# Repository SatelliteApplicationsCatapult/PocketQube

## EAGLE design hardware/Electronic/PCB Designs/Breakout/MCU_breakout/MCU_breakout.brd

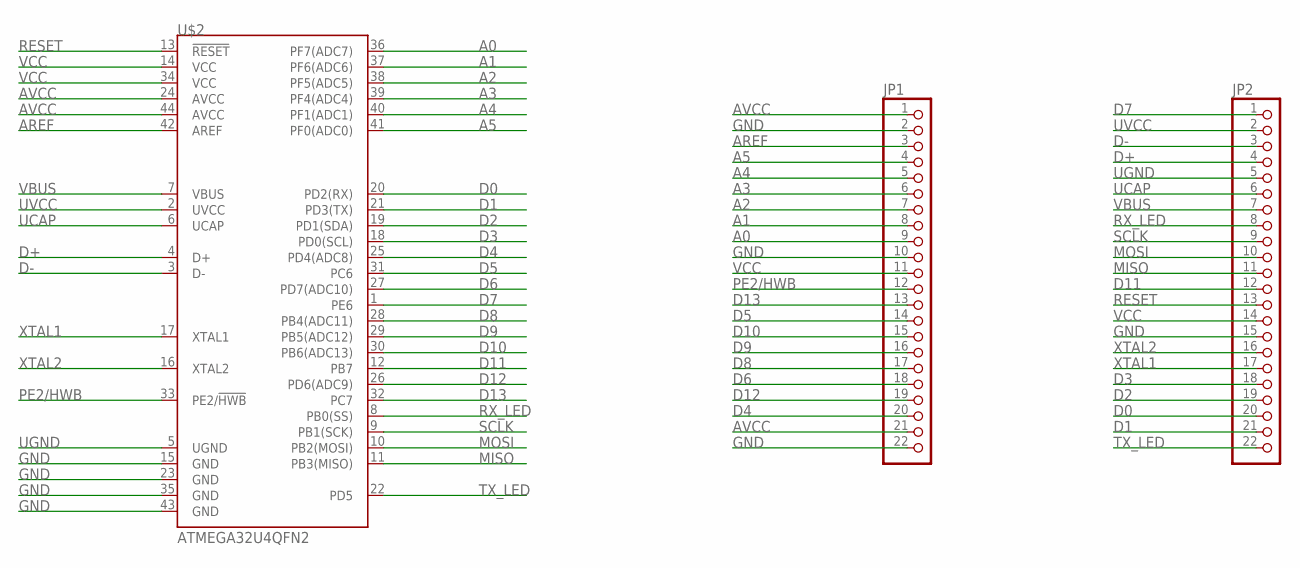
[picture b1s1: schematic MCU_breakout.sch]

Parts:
JP1, JP2: PINHD-1X22; 1X22
U$2: ATMEGA32U4QFN2; QFN-44-NOPAD

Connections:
A0: JP1.9, U$2.36 (PF7(ADC7))
A1: JP1.8, U$2.37 (PF6(ADC6))
A2: JP1.7, U$2.38 (PF5(ADC5))
A3: JP1.6, U$2.39 (PF4(ADC4))
A4: JP1.5, U$2.40 (PF1(ADC1))
A5: JP1.4, U$2.41 (PF0(ADC0))
AREF: JP1.3, U$2.42 (AREF)
AVCC: JP1.1, JP1.21, U$2.24 (AVCC), U$2.44 (AVCC)
D0: JP2.20, U$2.20 (PD2(RX))
D1: JP2.21, U$2.21 (PD3(TX))
D2: JP2.19, U$2.19 (PD1(SDA))
D3: JP2.18, U$2.18 (PD0(SCL))
D4: JP1.20, U$2.25 (PD4(ADC8))
D5: JP1.14, U$2.31 (PC6)
D6: JP1.18, U$2.27 (PD7(ADC10))
D7: JP2.1, U$2.1 (PE6)
D8: JP1.17, U$2.28 (PB4(ADC11))
D9: JP1.16, U$2.29 (PB5(ADC12))
D10: JP1.15, U$2.30 (PB6(ADC13))
D11: JP2.12, U$2.12 (PB7)
D12: JP1.19, U$2.26 (PD6(ADC9))
D13: JP1.13, U$2.32 (PC7)
D+: JP2.4, U$2.4 (D+)
D-: JP2.3, U$2.3 (D-)
GND: JP1.2, JP1.10, JP1.22, JP2.15, U$2.15 (GND), U$2.23 (GND), U$2.35 (GND), U$2.43 (GND)
MISO: JP2.11, U$2.11 (PB3(MISO))
MOSI: JP2.10, U$2.10 (PB2(MOSI))
PE2/HWB: JP1.12, U$2.33 (PE2/!HWB)
RESET: JP2.13, U$2.13 (!RESET)
RX_LED: JP2.8, U$2.8 (PB0(SS))
SCLK: JP2.9, U$2.9 (PB1(SCK))
TX_LED: JP2.22, U$2.22 (PD5)
UCAP: JP2.6, U$2.6 (UCAP)
UGND: JP2.5, U$2.5 (UGND)
UVCC: JP2.2, U$2.2 (UVCC)
VBUS: JP2.7, U$2.7 (VBUS)
VCC: JP1.11, JP2.14, U$2.14 (VCC), U$2.34 (VCC)
XTAL1: JP2.17, U$2.17 (XTAL1)
XTAL2: JP2.16, U$2.16 (XTAL2)

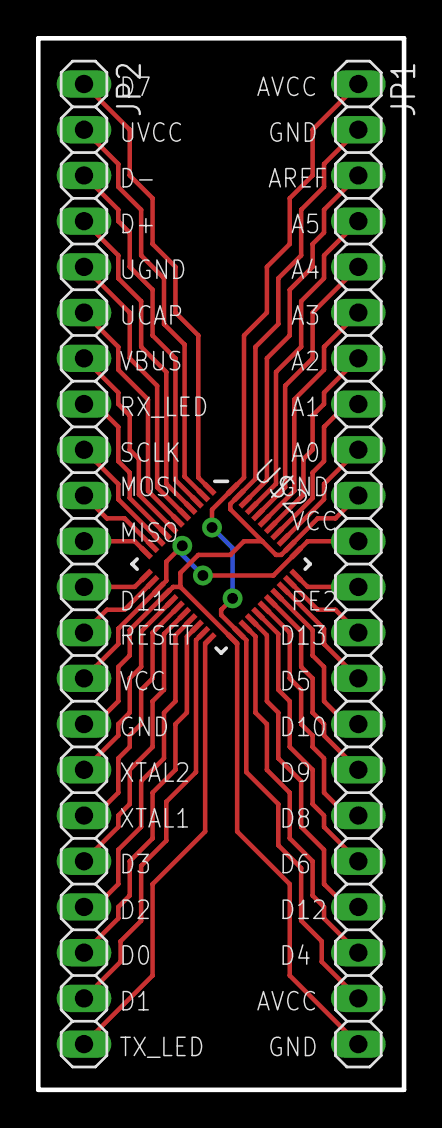
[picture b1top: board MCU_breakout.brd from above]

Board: 2 copper layers, 20.3 x 58.4 mm, 3 parts (0 on the bottom side), 39 nets.

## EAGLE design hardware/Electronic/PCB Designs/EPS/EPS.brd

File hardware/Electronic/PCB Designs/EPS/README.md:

# PQ60 Electrical Power System

### At a glance
The current EPS design features the following basic systems:

1. Four _IXYS_ solar panels as a power source

2. Two _LTC3105_ based MPPT circuits to maximise the solar power generated

3. A _MAX8606ETD_ charge management IC to facilitate safe battery charging and effective system load management.

4. A regulation circuit including:
	* A watchdog timer to detect unresponsive MCUs (_STWD100PYW83F_)
	* A brownout monitor to detect invalid voltages (_BU4231G-TR_)
	* A 3V3 LDO regulator with active-high enable, allowing supervisor ICs or external MCUs to trigger a reset (_MIC5353-3.3YMT_)
	
5. Current monitoring:
	* _FAN4010IL6X_F113_ based high-side unidirectional current sense amplifier ICs to monitor solar output, total 3V3 draw and draw from the battery voltage line on the PQ60 bus
	* _INA211A_ based high-side bi-directional current sense amplifier to monitor total current draw and supply to the battery
	
6. Voltage monitoring:
	* Two MOSFET switched divider networks to measure the MPPT output voltage, the raw battery voltage
	* Direct measurement through MCU ADC of the 3V3 bus voltage
	
7. A 650mAh 3.7V single cell lithium polymer battery

8. Five high-side MOSFET (_NTA4151P & FK3303010L_) switched lines for the __PQ60__ standard, three 3V3 and two raw battery voltage. Each line is reverse polarity protected by the MOSFET and over current protected by a resettable polyfuse (_1206L025YR_)

9. A single _MKL02Z32VFM4_ 32 bit Kinetis MCU, for power management, current and voltage monitoring, line switching and communication with the OBC through I2C

### Usage
Will write something in this section once we actually have an EPS and some code to go with it. Maybe unnecessary if all dealt with through cube library? Will list maximum ratings, tolerances and so on.

### Current design
The current revision of the EPS board uses four __IXYS__ solar panels (_SLMD121H10L-ND_) as a power source, or can also be charged from a standard USB supply. The board contains two Maximum Power Point Tracker (MPPT) circuits based on the __LTC3105__ (_LTC3105EDD#PBF_) DC-DC switching boost regulator, sharing two panels each, with a low forward voltage drop schottkey diode to prevent reverse current leakage from the panels while not illuminated. The output of the MPPT circuits is fed through a twin channel MOSFET based ideal diode IC (_LTC4413_) to the charge management IC (_MAX8606ETD+T_). The total current produced by the MPPT circuits and delivered to the charging IC is monitored by a high side current sense amplifier (_FAN4010IL6X_), and the supply voltage can be measured through a resistor divider network. A MOSFET exists (_NX7002AK_) to disable this divider circuit to prevent current draw when not required. The charge management IC includes integrated load servicing. When the battery voltage exceeds 3.5V, the system output will be internally connected to the battery. Below this voltage, the power supply to the IC will first be used to service the system load, with the remaining available current being used to charge the battery. Both charging sources, the MPPTs and the USB supply, can be disabled if required, in order to obtain accurate battery voltage measurements. The MPPTs can be disabled through a signal to the SHDN input, and the USB supply is connected through a high side switched MOSFET circuit to enable disconnecting. The SHDN signal to the _LTC3105_ MPPTs is connected through an opto-isolator to allow recovery in the event of a fully discharged battery.

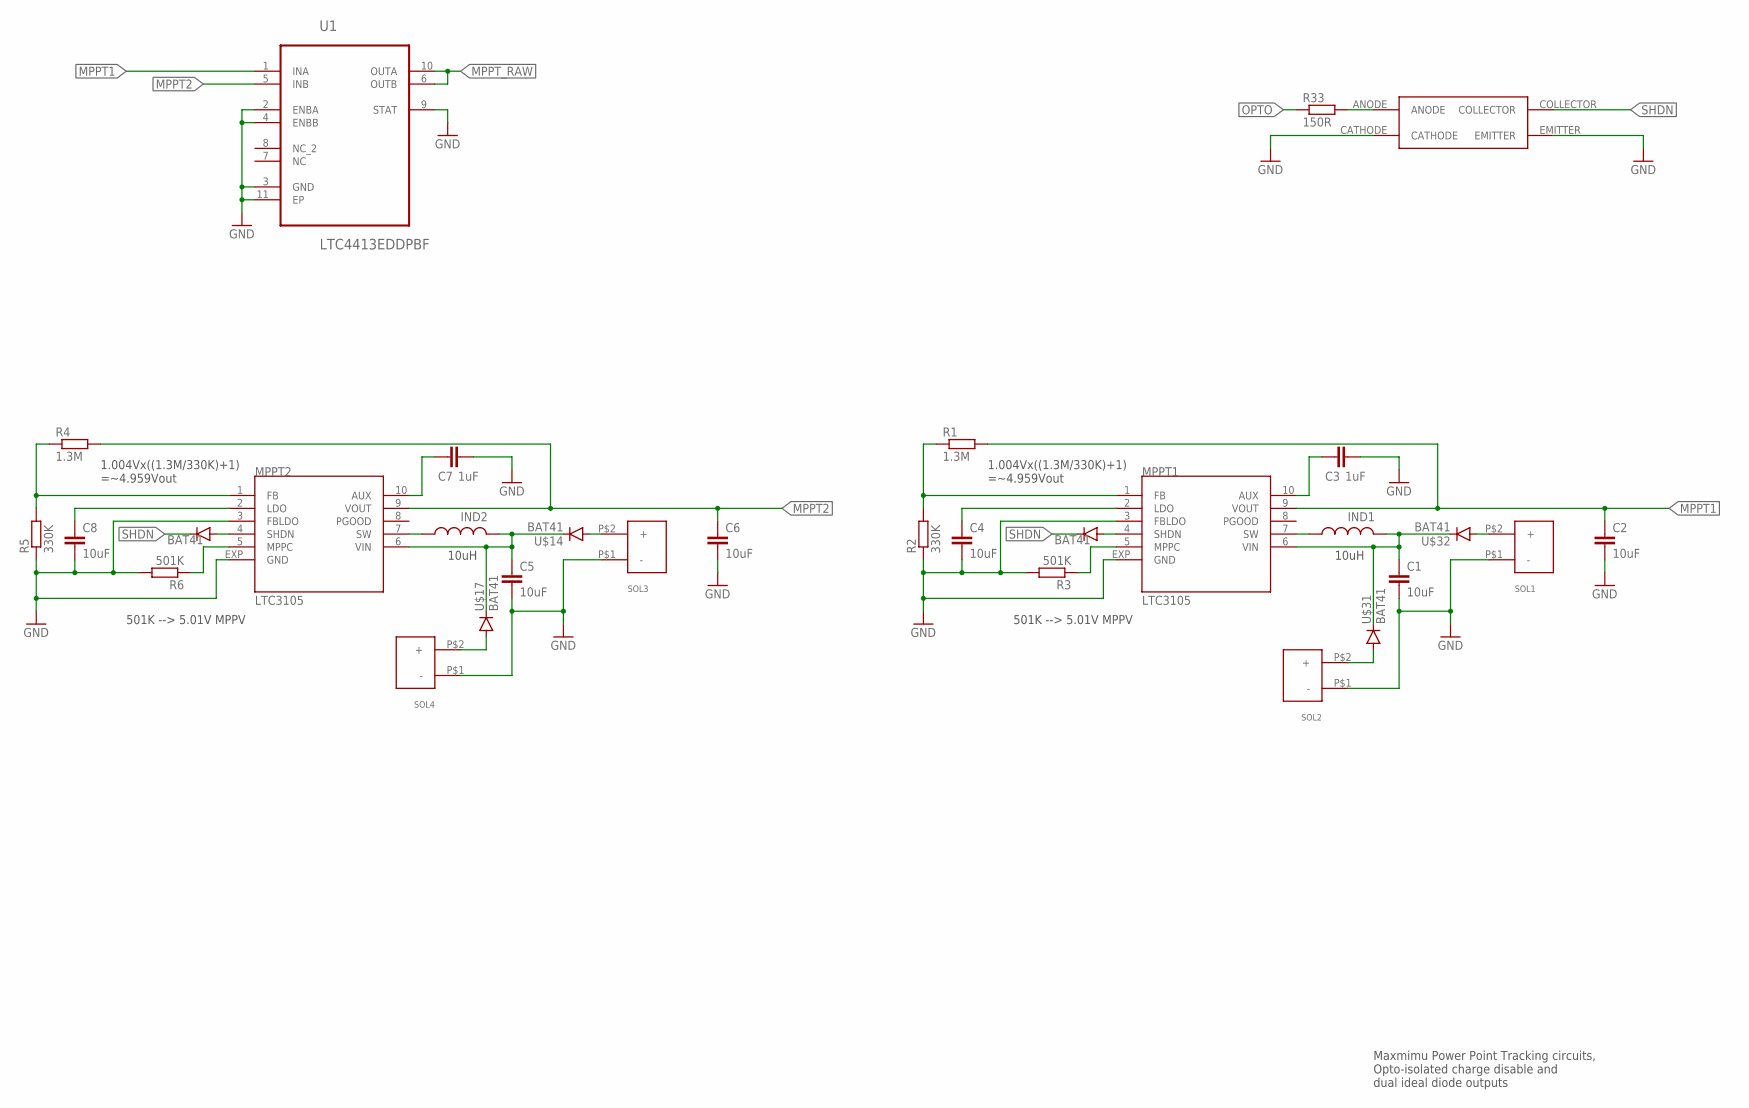
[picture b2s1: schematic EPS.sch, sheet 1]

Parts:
C1, C2, C4, C5, C6, C8: 10uF; C0603
C3, C7: 1uF; C0402
IND1, IND2: WE-TPC-744031100
MPPT1, MPPT2: LTC3105; DFN-3X3
R1, R4: 1.3M; R0402
R2, R5: 330K; R0402
R3, R6: 501K; R0402
R33: 150R; R0402
SOL1, SOL2, SOL3, SOL4: JST-B2B-ZH; JST-B2B-ZR
U1: LTC4413EDDPBF; DFN300X300X80-11N
U$4, U$10, U$14, U$17, U$31, U$32: BAT41; SOD-123
U$24: EL3H7

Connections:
GND: C1.2, C2.2, C3.2, C4.2, C5.2, C6.2, C7.2, C8.2, MPPT1.3 (FBLDO), MPPT1.EXP (GND), MPPT2.3 (FBLDO), MPPT2.EXP (GND), R2.1, R3.2, R5.1, R6.2, SOL1.P$1 (-), SOL2.P$1 (-), SOL3.P$1 (-), SOL4.P$1 (-), U1.2 (ENBA), U1.3 (GND), U1.4 (ENBB), U1.9 (STAT), U1.11 (EP), U$24.CATHODE, U$24.EMITTER; also elsewhere on the board
MPPT1: C2.1, MPPT1.9 (VOUT), R1.2, U1.1 (INA)
MPPT2: C6.1, MPPT2.9 (VOUT), R4.2, U1.5 (INB)
MPPT_RAW: U1.6 (OUTB), U1.10 (OUTA); also elsewhere on the board
unnamed: IND1.P$1 (1), MPPT1.7 (SW)
unnamed: C1.1, IND1.P$3 (2), MPPT1.6 (VIN), U$31.P$1 (C), U$32.P$1 (C)
unnamed: IND2.P$1 (1), MPPT2.7 (SW)
unnamed: C3.1, MPPT1.10 (AUX)
unnamed: C7.1, MPPT2.10 (AUX)
unnamed: C5.1, IND2.P$3 (2), MPPT2.6 (VIN), U$14.P$1 (C), U$17.P$1 (C)
unnamed: MPPT2.1 (FB), R4.1, R5.2
unnamed: C4.1, MPPT1.2 (LDO)
unnamed: MPPT1.1 (FB), R1.1, R2.2
unnamed: MPPT2.5 (MPPC), R6.1
unnamed: C8.1, MPPT2.2 (LDO)
unnamed: MPPT2.4 (SHDN), U$10.P$2 (A)
unnamed: SOL4.P$2 (+), U$17.P$2 (A)
unnamed: MPPT1.4 (SHDN), U$4.P$2 (A)
unnamed: MPPT1.5 (MPPC), R3.1
unnamed: SOL3.P$2 (+), U$14.P$2 (A)
unnamed: SOL2.P$2 (+), U$31.P$2 (A)
unnamed: SOL1.P$2 (+), U$32.P$2 (A)
unnamed: R33.2, U$24.ANODE
OPTO: R33.1; also elsewhere on the board
SHDN: U$4.P$1 (C), U$10.P$1 (C), U$24.COLLECTOR

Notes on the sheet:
10uH
501K --> 5.01V MPPV
1.004Vx((1.3M/330K)+1) =~4.959Vout
Maxmimu Power Point Tracking circuits, Opto-isolated charge disable and dual ideal diode outputs

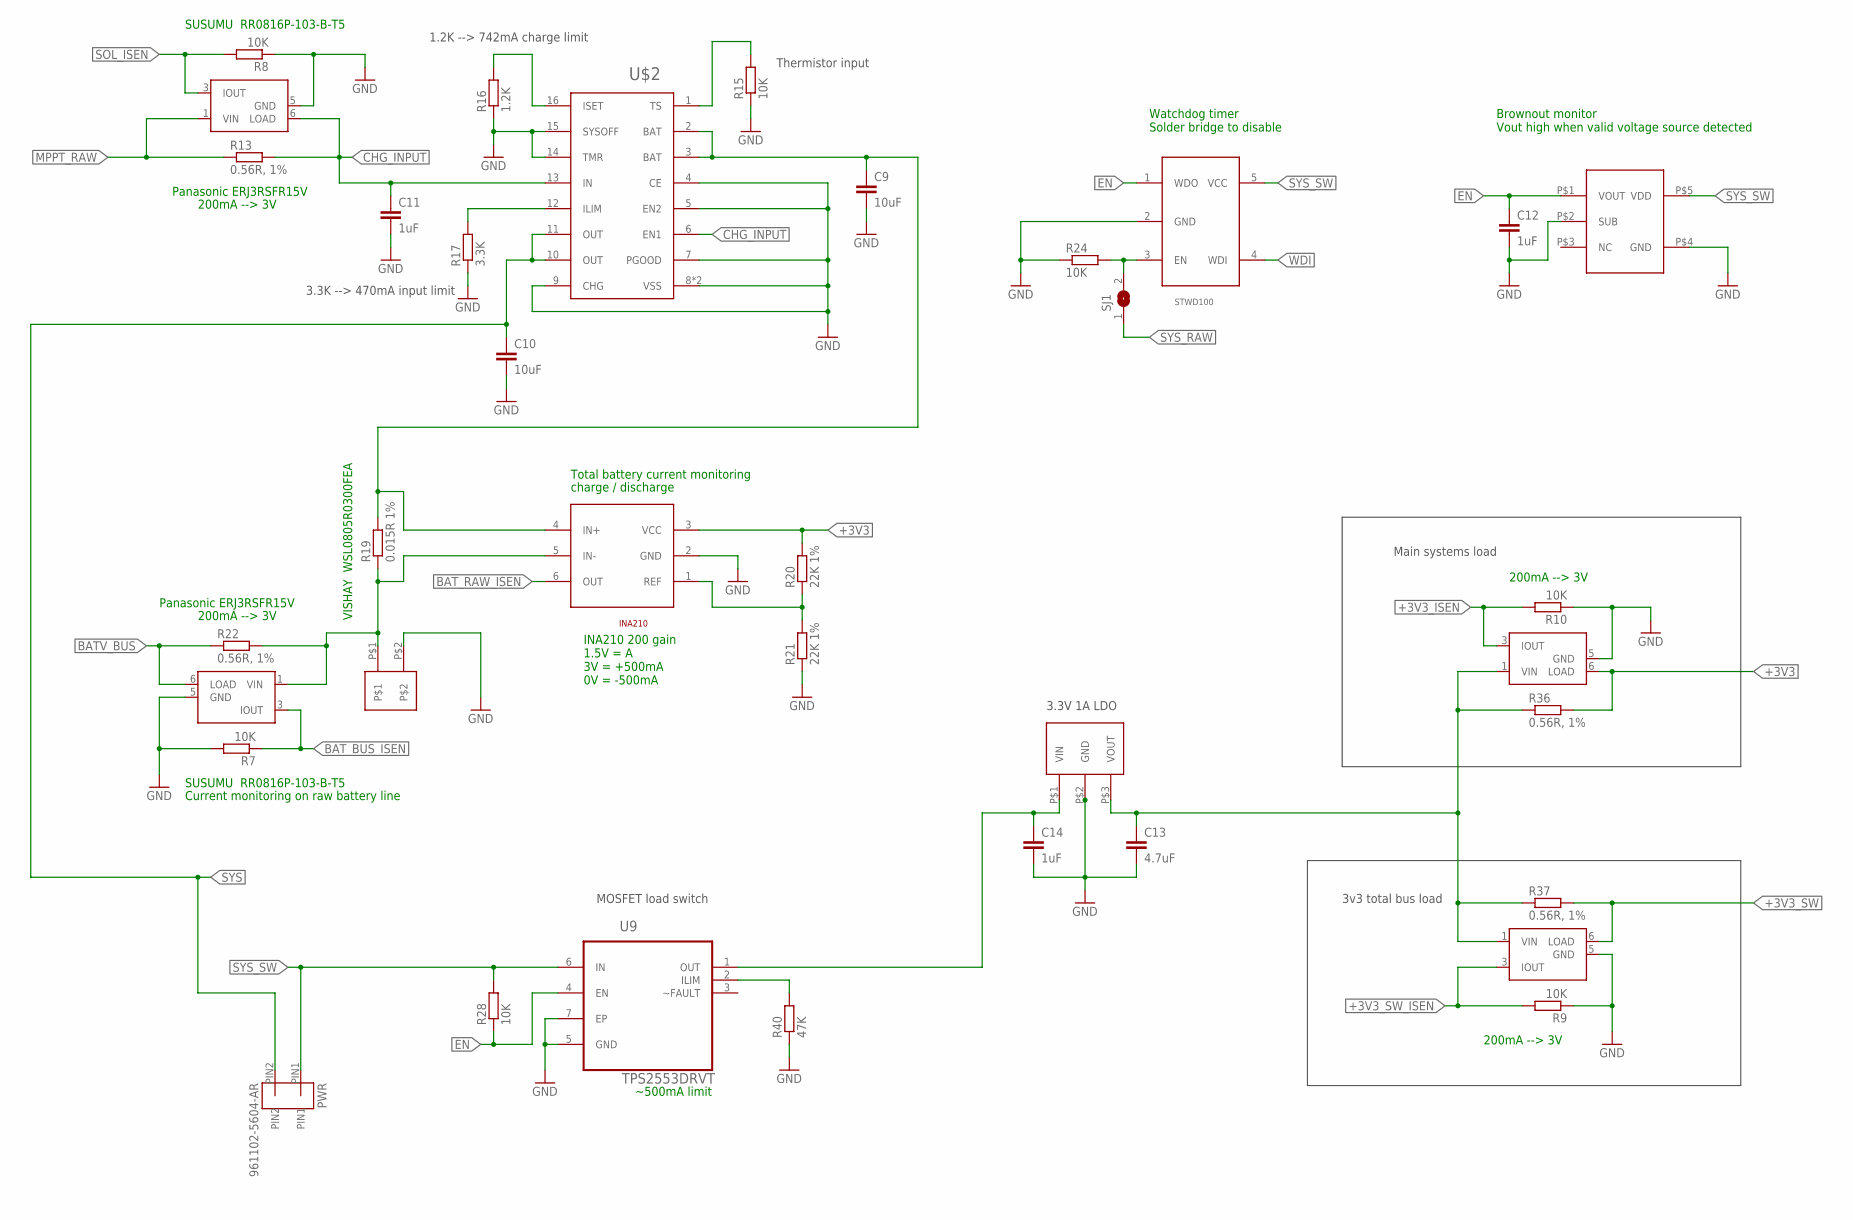
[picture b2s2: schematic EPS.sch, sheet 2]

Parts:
C9, C10: 10uF; C0805
C11, C12, C14: 1uF; C0603
C13: 4.7uF; C0805
INA210: INA211A; SC-70
PWR: 961102-5604-AR
R7, R8, R9, R10, R15, R24, R28: 10K; R0402
R13, R22, R36, R37: 0.56R, 1%; R0603
R16: 1.2K; R0402
R17: 3.3K; R0402
R19: 0.015R 1%; R0603
R20, R21: 22K 1%; R0402
R40: 47K; R0402
SJ1: SJ
STWD100: STWD100PYW83F; SOT_323-5
U9: TPS2553DRVT; SON65P200X200X80-7N
U$2: BQ24079; PVQFN16-THERM
U$3: PICOBLADE53047
U$18, U$19, U$25, U$26: FAN4010IL6X_F113
U$20: MCP1826S; SOT223-3
U$29: BD4835FVE; VSOF5

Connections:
+3V3: INA210.3 (VCC), R20.2, R36.2, U$25.6 (LOAD); also elsewhere on the board
+3V3_ISEN: R10.2, U$25.3 (IOUT); also elsewhere on the board
+3V3_REG: C13.1, R36.1, R37.1, U$20.P$3 (VOUT), U$25.1 (VIN), U$26.1 (VIN)
+3V3_SW: R37.2, U$26.6 (LOAD); also elsewhere on the board
+3V3_SW_ISEN: R9.2, U$26.3 (IOUT); also elsewhere on the board
BATV_BUS: R22.1, U$19.6 (LOAD); also elsewhere on the board
BAT_BUS_ISEN: R7.1, U$19.3 (IOUT); also elsewhere on the board
BAT_RAW_ISEN: INA210.6 (OUT); also elsewhere on the board
CHG_INPUT: C11.1, R13.2, U$2.6 (EN1), U$2.13 (IN), U$18.6 (LOAD); also elsewhere on the board
EN: C12.1, R28.1, STWD100.1 (WDO), U9.4 (EN), U$29.P$1 (VOUT); also elsewhere on the board
GND: C9.2, C10.2, C11.2, C12.2, C13.2, C14.2, INA210.2 (GND), R7.2, R8.1, R9.1, R10.1, R15.1, R16.1, R17.1, R21.1, R24.1, R40.1, STWD100.2 (GND), U9.5 (GND), U9.7 (EP), U$2.4 (CE), U$2.5 (EN2), U$2.7 (PGOOD), U$2.8 (VSS), U$2.9 (CHG), U$2.14 (TMR), U$2.15 (SYSOFF), U$2.17 (VSS), U$3.P$2, U$18.5 (GND), U$19.5 (GND), U$20.P$2 (GND), U$20.P$4 (GND), U$25.5 (GND), U$26.5 (GND), U$29.P$2 (SUB), U$29.P$4 (GND); also elsewhere on the board
MPPT_RAW: R13.1, U$18.1 (VIN); also elsewhere on the board
unnamed: C14.1, U9.1 (OUT), U$20.P$1 (VIN)
unnamed: C9.1, INA210.4 (IN+), R19.2, U$2.2 (BAT), U$2.3 (BAT)
unnamed: R15.2, U$2.1 (TS)
unnamed: R16.2, U$2.16 (ISET)
unnamed: R17.2, U$2.12 (ILIM)
unnamed: INA210.5 (IN-), R19.1, R22.2, U$3.P$1, U$19.1 (VIN)
unnamed: INA210.1 (REF), R20.1, R21.2
unnamed: R24.2, SJ1.2, STWD100.3 (EN)
unnamed: R40.2, U9.2 (ILIM)
SOL_ISEN: R8.2, U$18.3 (IOUT); also elsewhere on the board
SYS: C10.1, PWR.PIN2, U$2.10 (OUT), U$2.11 (OUT)
SYS_RAW: SJ1.1
SYS_SW: PWR.PIN1, R28.2, STWD100.5 (VCC), U9.6 (IN), U$29.P$5 (VDD)
WDI: STWD100.4 (WDI); also elsewhere on the board

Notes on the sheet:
Panasonic ERJ3RSFR15V
200mA --> 3V
SUSUMU RR0816P-103-B-T5
VISHAY WSL0805R0300FEA
Total battery current monitoring
charge / discharge
INA210 200 gain 1.5V = A 3V = +500mA 0V = -500mA
Current monitoring on raw battery line
Main systems load
3v3 total bus load
~500mA limit
Watchdog timer Solder bridge to disable
Brownout monitor Vout high when valid voltage source detected
MOSFET load switch
3.3V 1A LDO
1.2K --> 742mA charge limit
3.3K --> 470mA input limit
Thermistor input

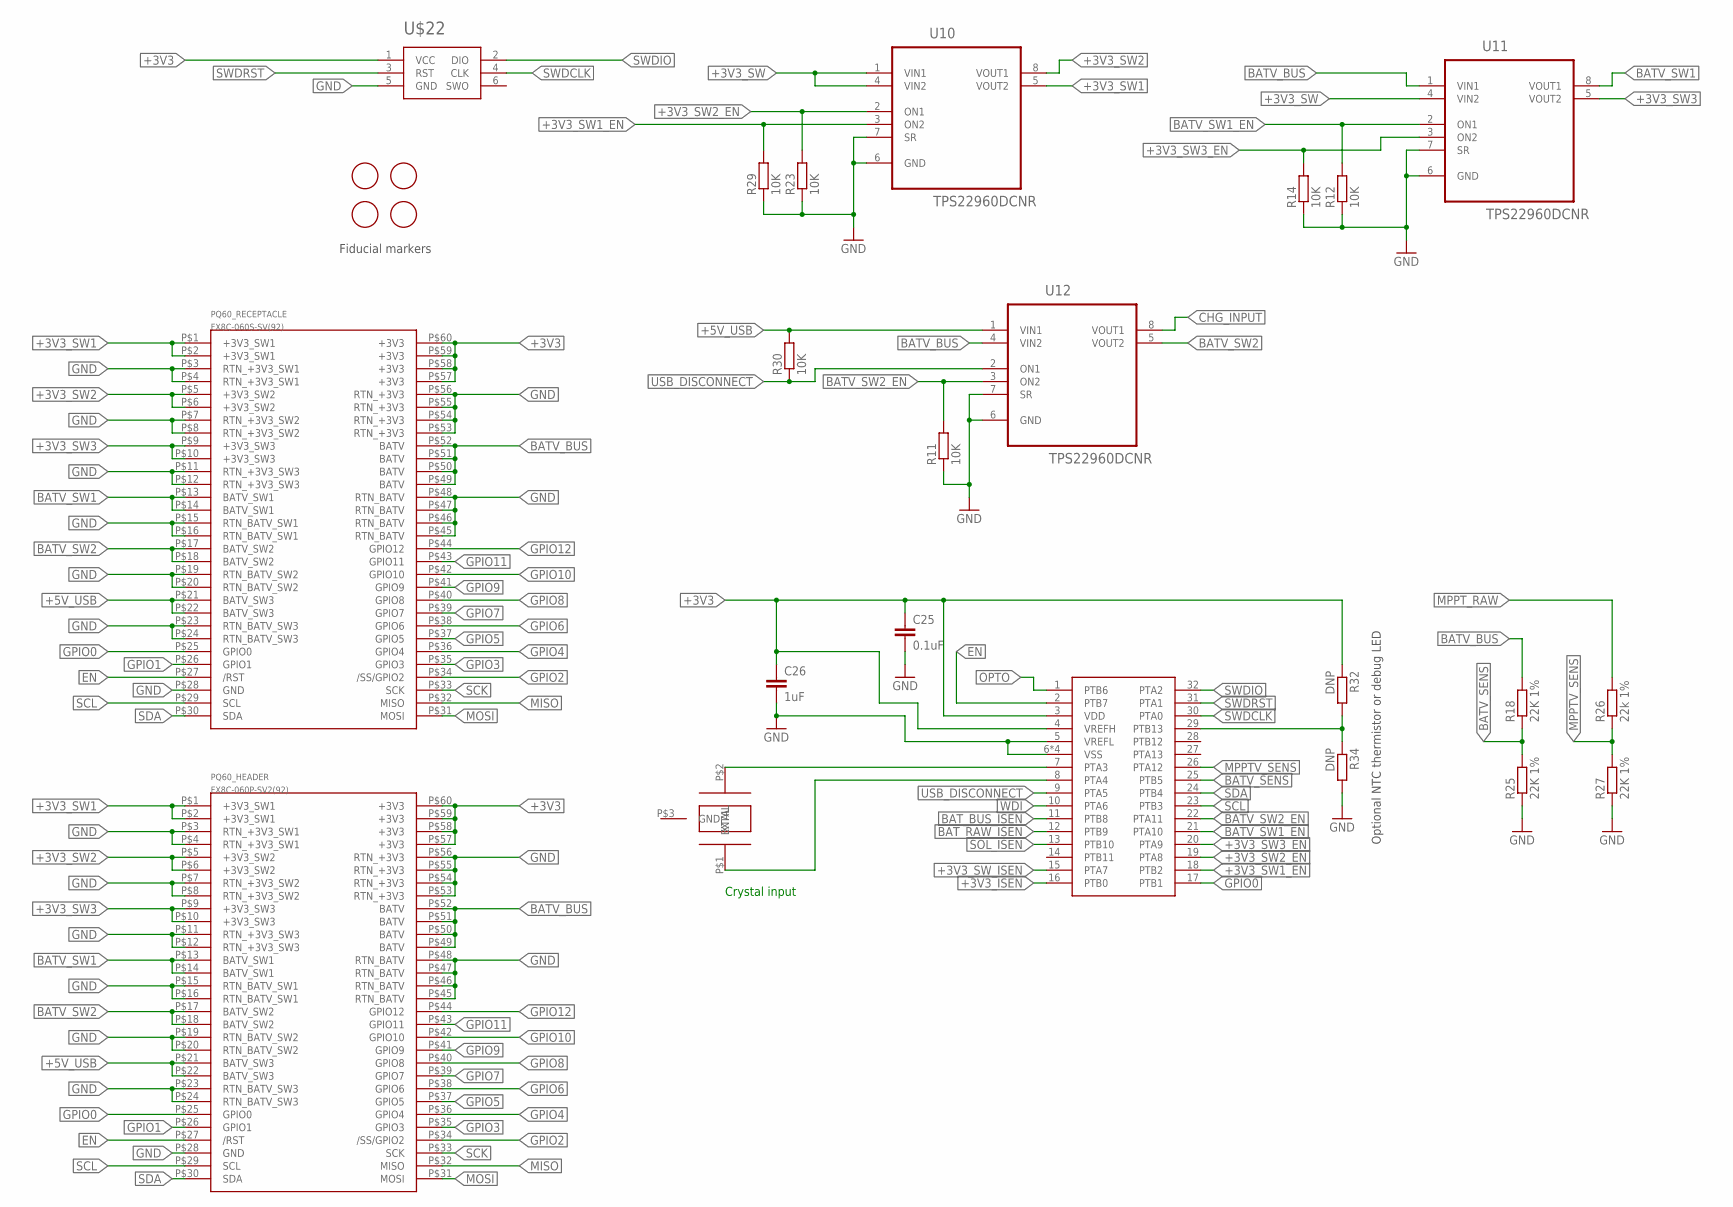
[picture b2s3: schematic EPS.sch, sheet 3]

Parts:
C25: 0.1uF; C0402
C26: 1uF; C0402
FD1, FD2, FD3, FD4: FIDUCIAL; FIDUCIAL_1MM
PQ60_HEADER: FX8C-060P-SV2(92); FX8C-060P-SV(92)
PQ60_RECEPTACLE: FX8C-060S-SV(92)
R11, R12, R14, R23, R29, R30: 10K; R0402
R18, R25, R27: 22K 1%; R0402
R26: 22k 1%; R0402
R32, R34: DNP; R0402
U10, U11, U12: TPS22960DCNR; SOT65P280X145-8N
U$1: AB26TRQ
U$21: MKL02Z16VFM4
U$22: TAG_CONNECT_NO_HOLES

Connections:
+3V3: C25.1, C26.1, PQ60_HEADER.P$57 (+3V3), PQ60_HEADER.P$58 (+3V3), PQ60_HEADER.P$59 (+3V3), PQ60_HEADER.P$60 (+3V3), PQ60_RECEPTACLE.P$57 (+3V3), PQ60_RECEPTACLE.P$58 (+3V3), PQ60_RECEPTACLE.P$59 (+3V3), PQ60_RECEPTACLE.P$60 (+3V3), R32.1, U$21.3 (VDD), U$21.4 (VREFH), U$22.1 (VCC); also elsewhere on the board
+3V3_ISEN: U$21.16 (PTB0); also elsewhere on the board
+3V3_SW: U10.1 (VIN1), U10.4 (VIN2), U11.4 (VIN2); also elsewhere on the board
+3V3_SW1: PQ60_HEADER.P$1 (+3V3_SW1), PQ60_HEADER.P$2 (+3V3_SW1), PQ60_RECEPTACLE.P$1 (+3V3_SW1), PQ60_RECEPTACLE.P$2 (+3V3_SW1), U10.5 (VOUT2)
+3V3_SW1_EN: R29.2, U10.3 (ON2), U$21.18 (PTB2)
+3V3_SW2: PQ60_HEADER.P$5 (+3V3_SW2), PQ60_HEADER.P$6 (+3V3_SW2), PQ60_RECEPTACLE.P$5 (+3V3_SW2), PQ60_RECEPTACLE.P$6 (+3V3_SW2), U10.8 (VOUT1)
+3V3_SW2_EN: R23.2, U10.2 (ON1), U$21.19 (PTA8)
+3V3_SW3: PQ60_HEADER.P$9 (+3V3_SW3), PQ60_HEADER.P$10 (+3V3_SW3), PQ60_RECEPTACLE.P$9 (+3V3_SW3), PQ60_RECEPTACLE.P$10 (+3V3_SW3), U11.5 (VOUT2)
+3V3_SW3_EN: R14.2, U11.3 (ON2), U$21.20 (PTA9)
+3V3_SW_ISEN: U$21.15 (PTA7); also elsewhere on the board
+5V_USB: PQ60_HEADER.P$21 (BATV_SW3), PQ60_HEADER.P$22 (BATV_SW3), PQ60_RECEPTACLE.P$21 (BATV_SW3), PQ60_RECEPTACLE.P$22 (BATV_SW3), R30.2, U12.1 (VIN1)
BATV_BUS: PQ60_HEADER.P$49 (BATV), PQ60_HEADER.P$50 (BATV), PQ60_HEADER.P$51 (BATV), PQ60_HEADER.P$52 (BATV), PQ60_RECEPTACLE.P$49 (BATV), PQ60_RECEPTACLE.P$50 (BATV), PQ60_RECEPTACLE.P$51 (BATV), PQ60_RECEPTACLE.P$52 (BATV), R18.2, U11.1 (VIN1), U12.4 (VIN2); also elsewhere on the board
BATV_SENS: R18.1, R25.2, U$21.25 (PTB5)
BATV_SW1: PQ60_HEADER.P$13 (BATV_SW1), PQ60_HEADER.P$14 (BATV_SW1), PQ60_RECEPTACLE.P$13 (BATV_SW1), PQ60_RECEPTACLE.P$14 (BATV_SW1), U11.8 (VOUT1)
BATV_SW1_EN: R12.2, U11.2 (ON1), U$21.21 (PTA10)
BATV_SW2: PQ60_HEADER.P$17 (BATV_SW2), PQ60_HEADER.P$18 (BATV_SW2), PQ60_RECEPTACLE.P$17 (BATV_SW2), PQ60_RECEPTACLE.P$18 (BATV_SW2), U12.5 (VOUT2)
BATV_SW2_EN: R11.2, U12.3 (ON2), U$21.22 (PTA11)
BAT_BUS_ISEN: U$21.11 (PTB8); also elsewhere on the board
BAT_RAW_ISEN: U$21.12 (PTB9); also elsewhere on the board
CHG_INPUT: U12.8 (VOUT1); also elsewhere on the board
EN: PQ60_HEADER.P$27 (/RST), PQ60_RECEPTACLE.P$27 (/RST), U$21.2 (PTB7); also elsewhere on the board
GND: C25.2, C26.2, PQ60_HEADER.P$3 (RTN_+3V3_SW1), PQ60_HEADER.P$4 (RTN_+3V3_SW1), PQ60_HEADER.P$7 (RTN_+3V3_SW2), PQ60_HEADER.P$8 (RTN_+3V3_SW2), PQ60_HEADER.P$11 (RTN_+3V3_SW3), PQ60_HEADER.P$12 (RTN_+3V3_SW3), PQ60_HEADER.P$15 (RTN_BATV_SW1), PQ60_HEADER.P$16 (RTN_BATV_SW1), PQ60_HEADER.P$19 (RTN_BATV_SW2), PQ60_HEADER.P$20 (RTN_BATV_SW2), PQ60_HEADER.P$23 (RTN_BATV_SW3), PQ60_HEADER.P$24 (RTN_BATV_SW3), PQ60_HEADER.P$28 (GND), PQ60_HEADER.P$45 (RTN_BATV), PQ60_HEADER.P$46 (RTN_BATV), PQ60_HEADER.P$47 (RTN_BATV), PQ60_HEADER.P$48 (RTN_BATV), PQ60_HEADER.P$53 (RTN_+3V3), PQ60_HEADER.P$54 (RTN_+3V3), PQ60_HEADER.P$55 (RTN_+3V3), PQ60_HEADER.P$56 (RTN_+3V3), PQ60_RECEPTACLE.P$3 (RTN_+3V3_SW1), PQ60_RECEPTACLE.P$4 (RTN_+3V3_SW1), PQ60_RECEPTACLE.P$7 (RTN_+3V3_SW2), PQ60_RECEPTACLE.P$8 (RTN_+3V3_SW2), PQ60_RECEPTACLE.P$11 (RTN_+3V3_SW3), PQ60_RECEPTACLE.P$12 (RTN_+3V3_SW3), PQ60_RECEPTACLE.P$15 (RTN_BATV_SW1), PQ60_RECEPTACLE.P$16 (RTN_BATV_SW1), PQ60_RECEPTACLE.P$19 (RTN_BATV_SW2), PQ60_RECEPTACLE.P$20 (RTN_BATV_SW2), PQ60_RECEPTACLE.P$23 (RTN_BATV_SW3), PQ60_RECEPTACLE.P$24 (RTN_BATV_SW3), PQ60_RECEPTACLE.P$28 (GND), PQ60_RECEPTACLE.P$45 (RTN_BATV), PQ60_RECEPTACLE.P$46 (RTN_BATV), PQ60_RECEPTACLE.P$47 (RTN_BATV), PQ60_RECEPTACLE.P$48 (RTN_BATV), PQ60_RECEPTACLE.P$53 (RTN_+3V3), PQ60_RECEPTACLE.P$54 (RTN_+3V3), PQ60_RECEPTACLE.P$55 (RTN_+3V3), PQ60_RECEPTACLE.P$56 (RTN_+3V3), R11.1, R12.1, R14.1, R23.1, R25.1, R27.1, R29.1, R34.2, U10.6 (GND), U10.7 (SR), U11.6 (GND), U11.7 (SR), U12.6 (GND), U12.7 (SR), U$21.5 (VREFL), U$21.6 (VSS), U$21.GND@1 (VSS), U$21.GND@2 (VSS), U$21.GND@3 (VSS), U$22.5 (GND); also elsewhere on the board
GPIO0: PQ60_HEADER.P$25 (GPIO0), PQ60_RECEPTACLE.P$25 (GPIO0), U$21.17 (PTB1)
GPIO1: PQ60_HEADER.P$26 (GPIO1), PQ60_RECEPTACLE.P$26 (GPIO1)
GPIO2: PQ60_HEADER.P$34 (/SS/GPIO2), PQ60_RECEPTACLE.P$34 (/SS/GPIO2)
GPIO3: PQ60_HEADER.P$35 (GPIO3), PQ60_RECEPTACLE.P$35 (GPIO3)
GPIO4: PQ60_HEADER.P$36 (GPIO4), PQ60_RECEPTACLE.P$36 (GPIO4)
GPIO5: PQ60_HEADER.P$37 (GPIO5), PQ60_RECEPTACLE.P$37 (GPIO5)
GPIO6: PQ60_HEADER.P$38 (GPIO6), PQ60_RECEPTACLE.P$38 (GPIO6)
GPIO7: PQ60_HEADER.P$39 (GPIO7), PQ60_RECEPTACLE.P$39 (GPIO7)
GPIO8: PQ60_HEADER.P$40 (GPIO8), PQ60_RECEPTACLE.P$40 (GPIO8)
GPIO9: PQ60_HEADER.P$41 (GPIO9), PQ60_RECEPTACLE.P$41 (GPIO9)
GPIO10: PQ60_HEADER.P$42 (GPIO10), PQ60_RECEPTACLE.P$42 (GPIO10)
GPIO11: PQ60_HEADER.P$43 (GPIO11), PQ60_RECEPTACLE.P$43 (GPIO11)
GPIO12: PQ60_HEADER.P$44 (GPIO12), PQ60_RECEPTACLE.P$44 (GPIO12)
MISO: PQ60_HEADER.P$32 (MISO), PQ60_RECEPTACLE.P$32 (MISO)
MOSI: PQ60_HEADER.P$31 (MOSI), PQ60_RECEPTACLE.P$31 (MOSI)
MPPTV_SENS: R26.1, R27.2, U$21.26 (PTA12)
MPPT_RAW: R26.2; also elsewhere on the board
unnamed: U$1.P$2 (EXTAL), U$21.7 (PTA3)
unnamed: R32.2, R34.1, U$21.29 (PTB13)
unnamed: U$1.P$1 (XTAL), U$21.8 (PTA4)
OPTO: U$21.1 (PTB6); also elsewhere on the board
SCK: PQ60_HEADER.P$33 (SCK), PQ60_RECEPTACLE.P$33 (SCK)
SCL: PQ60_HEADER.P$29 (SCL), PQ60_RECEPTACLE.P$29 (SCL), U$21.23 (PTB3)
SDA: PQ60_HEADER.P$30 (SDA), PQ60_RECEPTACLE.P$30 (SDA), U$21.24 (PTB4)
SOL_ISEN: U$21.13 (PTB10); also elsewhere on the board
SWDCLK: U$21.30 (PTA0), U$22.4 (CLK)
SWDIO: U$21.32 (PTA2), U$22.2 (DIO)
SWDRST: U$21.31 (PTA1), U$22.3 (RST)
USB_DISCONNECT: R30.1, U12.2 (ON1), U$21.9 (PTA5)
WDI: U$21.10 (PTA6); also elsewhere on the board

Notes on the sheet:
Fiducial markers
Optional NTC thermistor or debug LED
Crystal input

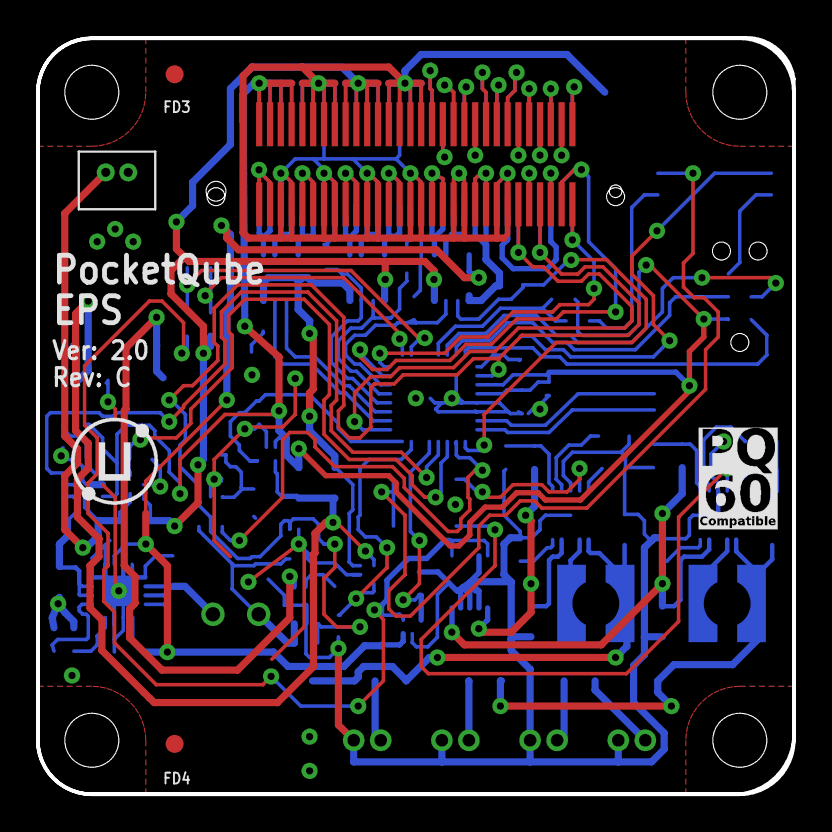
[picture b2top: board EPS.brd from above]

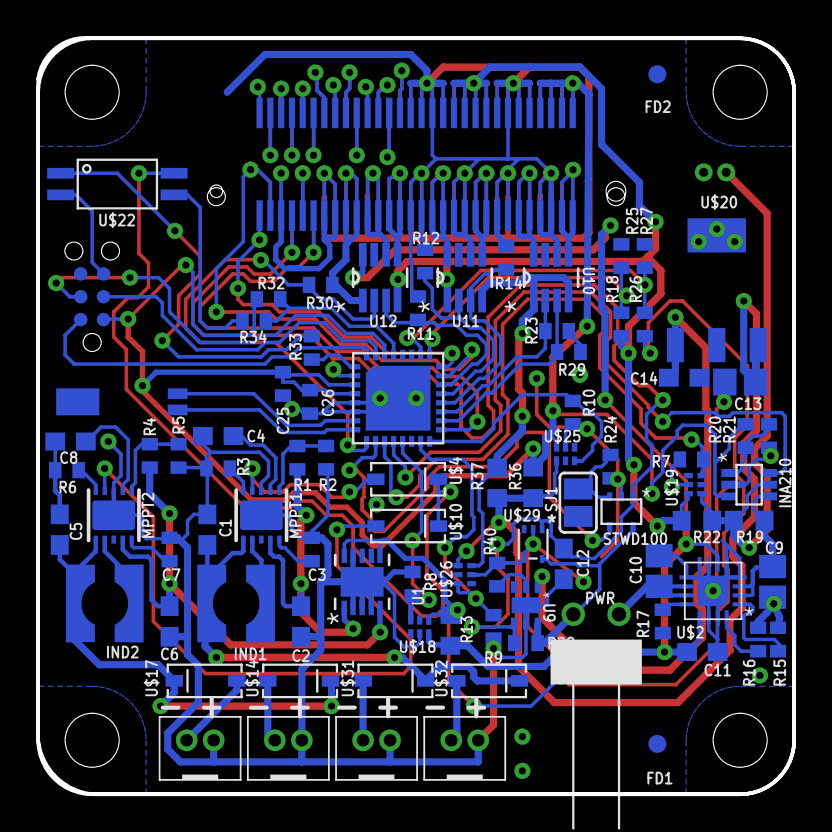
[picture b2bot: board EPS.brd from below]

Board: 2 copper layers, 42.0 x 42.0 mm, 96 parts (89 on the bottom side), 86 nets.

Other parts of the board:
U$9: SA_LOGO_SMALL
U$13: PQ60_CMP
U$35: UBO_LOGO

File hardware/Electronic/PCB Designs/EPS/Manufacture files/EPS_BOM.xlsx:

Parts | Manufacturer | Part number | Value | Qty | Package | Description | Distributor | Order code | Price per | Total | Notes | ROHS | Temp range
C1, C2, C4, C5, C6, C8 |  | C-EUC0603 | 10uF | 6 | C0603 | CAPACITOR, European symbol |  |  |  |  | Any compatible X7R MLCC
C11, C12, C14 |  | C-EUC0603 | 1uF | 3 | C0603 | CAPACITOR, European symbol |  |  |  |  | Any compatible X7R MLCC
C13 |  | C-EUC0805 | 4.7uF | 1 | C0805 | CAPACITOR, European symbol |  |  |  |  | Any compatible X7R MLCC
C25 |  | C-EUC0402 | 0.1uF | 1 | C0402 | CAPACITOR, European symbol |  |  |  |  | Any compatible X7R MLCC
C3, C7, C26 |  | C-EUC0402 | 1uF | 3 | C0402 | CAPACITOR, European symbol |  |  |  |  | Any compatible X7R MLCC
C9, C10 |  | C-EUC0805 | 10uF | 2 | C0805 | CAPACITOR, European symbol |  |  |  |  | Any compatible X7R MLCC
FD1, FD2, FD3, FD4 |  | FIDUCIAL |  | 4 | FIDUCIAL_1MM | For use by pick and place machines to calibrate the vision/machine, 1mm |  |  |  |  | Do not populate
INA210 | Texas Instruments | INA210AIDCKR |  | 1 | SC-70 | Current sense amplifier | Digi-key | 296-38954-1-ND | 1.1000000000000001 | 30.800000000000004 |  | Yes | -40 to 125
IND1, IND2 | Würth | 744031100 |  | 2 | WE-TPC-744031100 | Series Shielded Wire-wound SMD Inductor with a Ferrite Core | Digi-key | 732-1010-1-ND | 1.2230000000000001 | 68.488 | Alternative suppliers available | Yes | -40 to 125
MPPT1, MPPT2 | Linear Technology | LTC3105EMS#PBF |  | 2 | DFN-3X3 | Step-up DC/DC converter | Mouser | 584-LTC3105EMS#PBF | 3.56 | 199.36 |  | Yes | -40 to 85
PQ60_HEADER | Hirose | FX8C-60P-SV6(91) |  | 1 | FX8C-060P-SV(92) | Header | Mouser | 798-FX8C60PSV691 | 2.48 | 69.44 | Alternative suppliers available, however ensure the FX8C60PSV6 part is used, no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 | Yes
PQ60_RECEPTACLE | Hirose | FX8C-60S-SV(91) |  | 1 | FX8C-060S-SV(92) | Socket | Digi-key | H126151-ND | 2.7515999999999998 | 77.044799999999995 | Alternative suppliers available for FX8C60SSV | Yes
PWR | Molex | 90121-0762 |  | 1 | NA | PCB Header, 2.54mm pitch, right angle | Farnell | 9733442 | 0.39100000000000001 | 10.948 |  | Yes | -55 to 125
R1, R4 |  | R-EU_R0402 | 1.3M | 2 | R0402 | RESISTOR, European symbol |  |  |  |  | Any standard chip SMD resistor acceptable, 1% tolerance or better
R13, R22, R36, R37 | Panasonic | ERJ8RQFR56V | 0.56R, 1% | 4 | R0603 | RESISTOR, European symbol | Farnell | 1717849 | 0.14000000000000001 | 15.680000000000001 | Or compatible alternative | Yes | -55 to 125
R16 |  | R-EU_R0402 | 1.2K | 1 | R0402 | RESISTOR, European symbol |  |  |  |  | Any standard chip SMD resistor acceptable, 1% tolerance or better
R17 |  | R-EU_R0402 | 3.3K | 1 | R0402 | RESISTOR, European symbol |  |  |  |  | Any standard chip SMD resistor acceptable, 1% tolerance or better
R18, R20, R21, R25, R27 |  | R-EU_R0402 | 22K 1% | 5 | R0402 | RESISTOR, European symbol |  |  |  |  | Any standard chip SMD resistor acceptable, 1% tolerance or better
R19 | Panasonic | ERJ3BQFR30V | 0.015R 1% | 1 | R0603 | RESISTOR, European symbol | Farnell | 2692819 | 0.18 | 5.04 | Or compatible alternative
R2, R5 |  | R-EU_R0402 | 330K | 2 | R0402 | RESISTOR, European symbol |  |  |  |  | Any standard chip SMD resistor acceptable, 1% tolerance or better
R26 |  | R-EU_R0402 | 22k 1% | 1 | R0402 | RESISTOR, European symbol |  |  |  |  | Any standard chip SMD resistor acceptable, 1% tolerance or better
R3, R6 |  | R-EU_R0402 | 501K | 2 | R0402 | RESISTOR, European symbol |  |  |  |  | Any standard chip SMD resistor acceptable, 1% tolerance or better
R32, R34 |  | R-EU_R0402 |  | 2 | R0402 | RESISTOR, European symbol |  |  |  |  | Do not populate
R33 |  | R-EU_R0402 | 150R | 1 | R0402 | RESISTOR, European symbol |  |  |  |  | Any standard chip SMD resistor acceptable, 1% tolerance or better
R40 |  | R-EU_R0402 | 47K | 1 | R0402 | RESISTOR, European symbol |  |  |  |  | Any standard chip SMD resistor acceptable, 1% tolerance or better
R7, R8, R9, R10, R11, R12, R14, R15, R23, R24, R28, R29, R30 |  | R-EU_R0402 | 10K | 13 | R0402 | RESISTOR, European symbol |  |  |  |  | Any standard chip SMD resistor acceptable, 1% tolerance or better
SJ1 |  | SJ |  | 1 | SJ | SMD solder JUMPER |  |  |  |  | Do not populate
SOL1, SOL2, SOL3, SOL4 | JST | B2B-ZR(LF)(SN) |  | 4 | JST-B2B-ZR | 2-way crimp style Header Connector | Farnell | 9491775 | 6.9699999999999998E-2 | 6.97 | Alternative suppliers available | Yes | -25 to 85
STWD100 | STMicroelectronics | STWD100PYW83F |  | 1 | SOT_323-5 | Watchdog timer circuit | Farnell | 2460853RL | 0.67800000000000005 | 18.984000000000002 | Alternative suppliers available | Yes | -40 to 125
U$1 | Abracon LLC | AB26TRQ |  | 1 | AB26TRQ |  |  |  |  |  | Do not populate
U$18, U$19, U$25, U$26 | ON Semiconductor | FAN4010IL6X-F113 |  | 4 | FAN4010IL6X_F113 | Current sense amplifier | Farnell | 2454632 | 0.34100000000000003 | 38.192 | Alternative suppliers available | Yes | -40 to 85
U$2 | Texas Instruments | BQ24079RGTR |  | 1 | PVQFN16-THERM | Battery Charger for 1 Cell of Li-Ion battery | Farnell | 2492089 | 1.52 | 42.56 | Alternative suppliers available | Yes | -40 to 85
U$20 | Microchip | MCP1826S-3302E/DB |  | 1 | SOT223-3 | Fixed LDO Voltage Regulator | Farnell | 1578424 | 0.47899999999999998 | 13.411999999999999 | Alternative suppliers available | Yes | -40 to 125
U$21 | NXP | MKL02Z16VFM4 |  | 1 | MKL02Z16VFM4 | Microcontroller | Farnell | 2409469 | 1.83 | 51.24 | Alternative suppliers available | Yes | -55 to 150
U$22 |  | TAG_CONNECT_NO_HOLES |  | 1 | TAG_CONNECT_NO_HOLES |  |  |  |  |  | Do not populate
U$24 | Everlight Electronics | EL3H7(TA)-VG |  | 1 | EL3H7 | Phototransistor photocoupler | Digi-key | 1080-1198-1-ND | 0.30399999999999999 | 8.5120000000000005 | Alternative suppliers available | Yes | -55 to 125
U$29 | ROHM Semiconductor | BD4835FVE-TR |  | 1 | VSOF5 | CMOS voltage monitor | Mouser | 755-BD4835FVE-TR | 0.33900000000000002 | 9.4920000000000009 | Or compatible alternative | Yes | -40 to 105
U$3 | Molex | 53047-0210 |  | 1 | PICOBLADE53047 | Wire-to-board header | Farnell | 9733051 | 0.11899999999999999 | 3.3319999999999999 | Alternative suppliers available | Yes | -40 to 85
U$4, U$10, U$14, U$17, U$31, U$32 | STMicroelectronics | BAT41 |  | 6 | SOD-123 | Schottky diode | Farnell | 9801421 | 0.12 | 20.16 | Alternative suppliers available | Yes | -60 to 125
U1 | Linear Technology | LTC4413EDD#TRPBF |  | 1 | DFN300X300X80-11N | Dual 2.6A, 2.5V to 5.5V, Ideal Diodes | Digi-key | LTC4413EDD#PBF-ND | 2.8424 | 79.587199999999996 | Alternative suppliers available | Yes | -40 to 85
U10, U11, U12 | Texas Instruments | TPS22960DCNR |  | 3 | SOT65P280X145-8N | LOW INPUT VOLTAGE, DUAL LOAD SWITCH WITH CONTROLLED TURN-ON | Farnell | 3008910 | 0.621 | 52.164000000000001 | Alternative suppliers available | Yes | -40 to 85
U9 | Texas Instruments | TPS2553DRVT |  | 1 | SON65P200X200X80-7N | POWER-DISTRIBUTION SWITCHES | Mouser | 595-TPS2553DRVT | 1.45 | 40.6 | Alternative suppliers available | Yes | -40 to 85
 |  |  |  | Partlist exported from C:/Users/Ken.Diep/repos/hardware/Electronic/PCB Designs/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
 |  |  |  |  |  |  |  |  |  | 862.00599999999997

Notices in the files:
hardware/Electronic/PCB Designs/EPS/EPS.brd:
Copyright 2019 Satellite Applications Catapult
hardware/Electronic/PCB Designs/RFP/RFP.brd:
Copyright Satellite Applications Catapult 2019
parts and their libraries:
SparkFun-DigitalIC: Licensing: Creative Commons ShareAlike 4.0 International - https://creativecommons.org/licenses/by-sa/4.0
